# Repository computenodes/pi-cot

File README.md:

# Pi-iC880a

Adapter board to interface between the Raspberry Pi and the [iC880a LoRaWAN](https://wireless-solutions.de/products/radiomodules/ic880a.html) concentrator.  It also supports an EEPROM for HAT identification, DS3231 RTC chip for maintaining time between powercycles, and a [DHT-22](http://www.hobbytronics.co.uk/rht03-humidity-temp-sensor?keyword=dht22) for temperature/humidity sensing.

This board supports using 3 different GPS modules for the timing/positioning
 1. [Adafruit Ultimate GPS module](https://www.adafruit.com/product/746) soldered onto the board.  
 1. The MT3339 GPS modules (as used on the adafruit break out board) soldered directly to the PCB.  
 1. Ublox LEA-6T soldered onto the iC880a Concentrator.
 
 ## GPS Options
 In order to support the different GPS options there are solder jumpers on the PCB to link the required lines.  There are 3 jumpers: TX, RX, PPS.  The jumpers for TX & RX need to be used whichever GPS module is in use.  The PPS link is needed if using either the Ultimate GPS, or the MT3339.
 
 ## Backup battery options
 There are also pads for 0 ohm resistors to enable a choice of which peripherals have the backup battery connected.  These can either be popuplated with 0ohm resistors, or just bridged using solder.
 
 ## Enabling the UBlox module
 All GPIOs from the iC880a board are connected to the Pi.  In order to enable the UBlox module on the iC880a a couple of these need to be configured as shown below.
 
 | Pi I/O | Function | Pin State |
 | ------ | -------- | --------- |
 |  23    |  GPS  EN | HIGH      |
 |  27    | !GPS RST | HIGH      |

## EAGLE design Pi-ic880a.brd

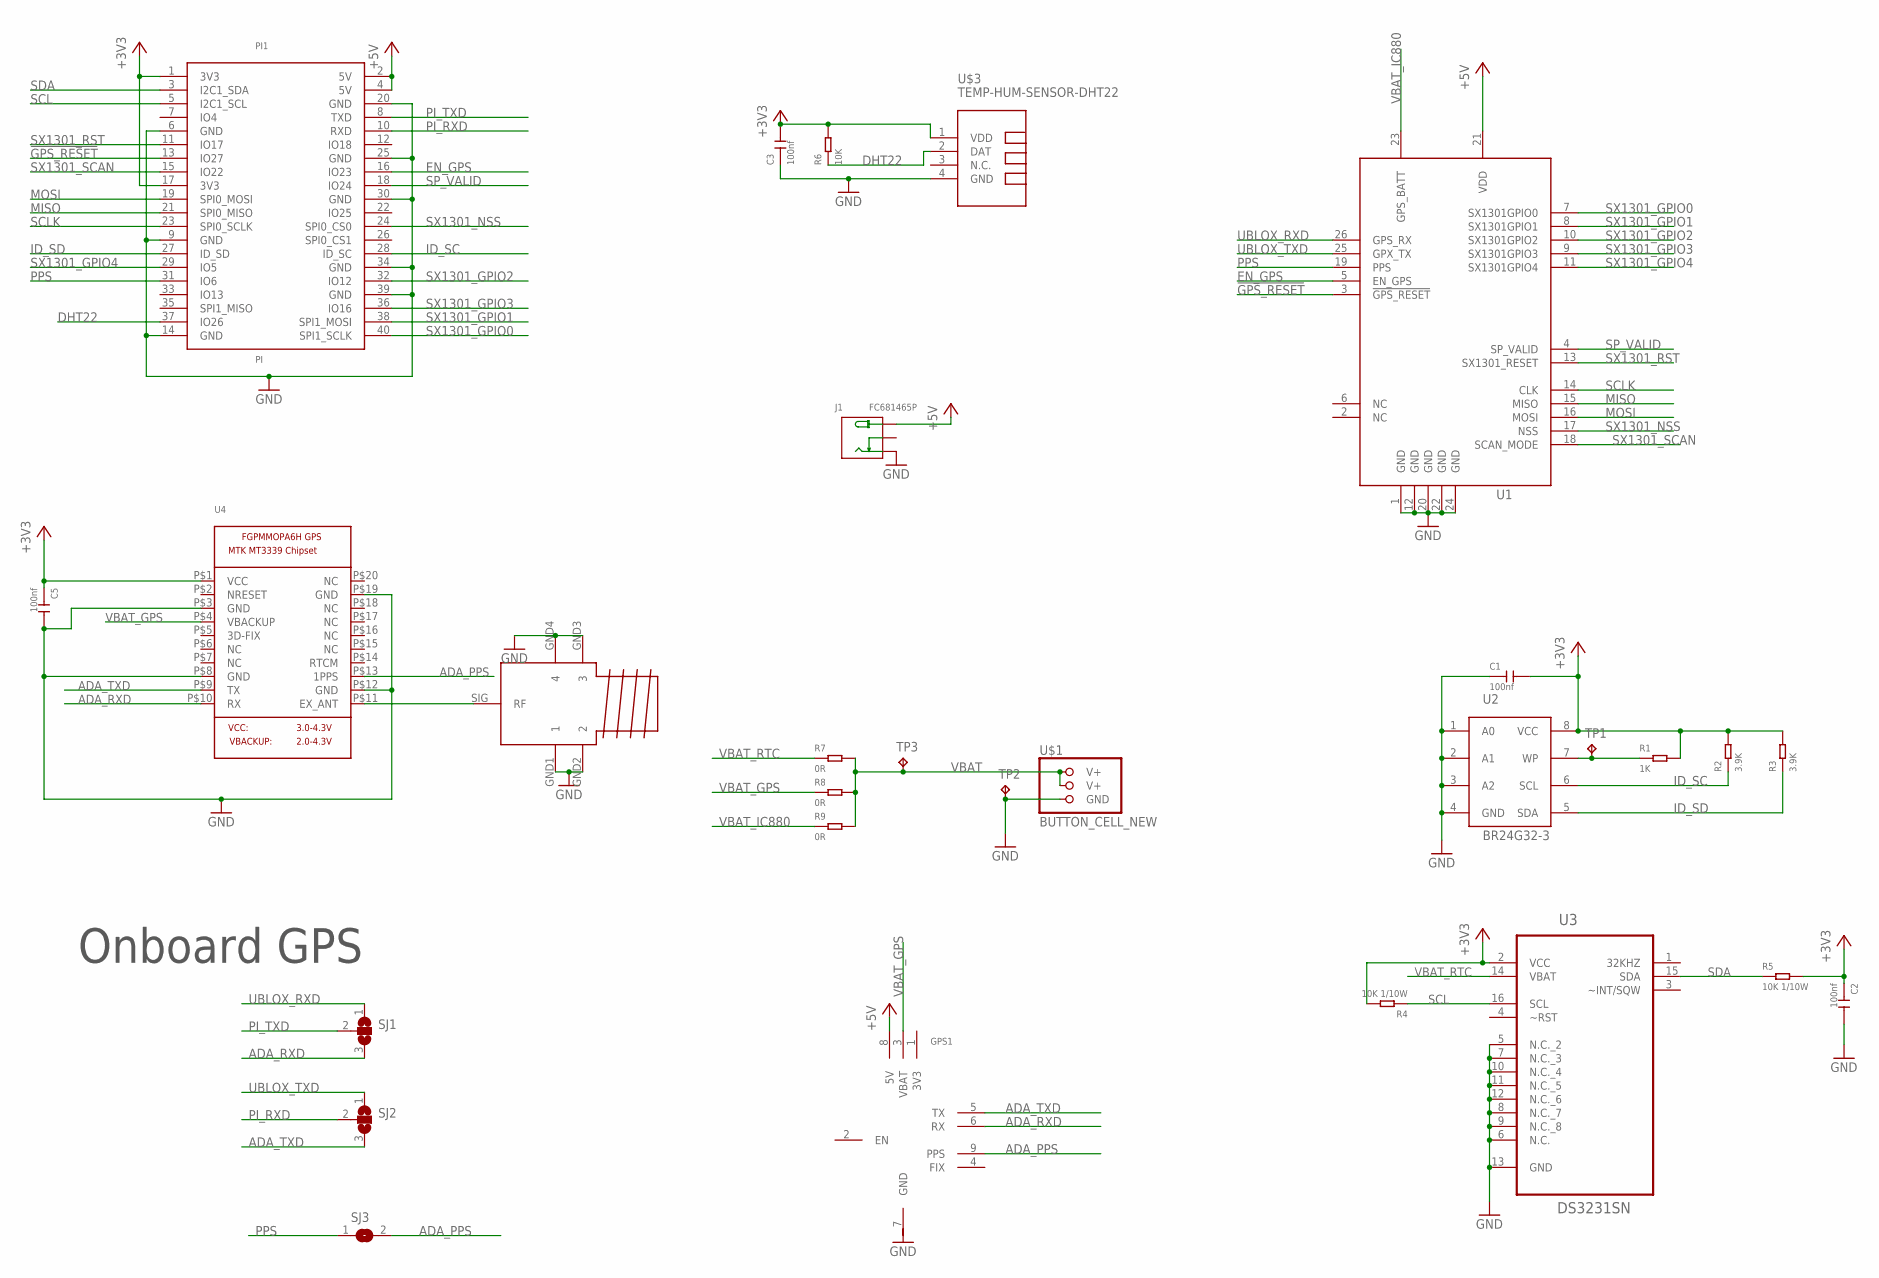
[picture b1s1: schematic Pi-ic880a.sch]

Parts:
C1, C2, C3, C5: 100nf; C0603
GPS1: ULTIMATE-GPS
J1: FC681465P
PI1: PI
R1: 1K; R0603
R2, R3: 3.9K; R0603
R4, R5: 10K 1/10W; R0603
R6: 10K; R0603
R7, R8, R9: 0R; R0603
SJ1, SJ2: SJ2W; SJ_2
SJ3: SJ
TP1, TP2, TP3: TPB2,54; B2,54
U1: IC880A
U2: BR24G32-3; SOP8
U3: DS3231SN; SOIC127P1032X265-16N
U4: GPS_FGPMMOPA6H; FGPMMOPA6H
U$1: BUTTON_CELL_NEW; CR2016
U$2: SMATH; SMA
U$3: TEMP-HUM-SENSOR-DHT22

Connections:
3V3: GPS1.1 (3V3)
!GPS_RESET: PI1.13 (IO27), U1.3 (!GPS_RESET)
+3V3: C1.2, C2.1, C3.2, C5.1, PI1.1 (3V3), PI1.17 (3V3), R1.2, R2.2, R3.2, R4.2, R5.2, R6.2, U2.8 (VCC), U3.2 (VCC), U4.P$1 (VCC), U$3.1 (VDD)
+5V: GPS1.8 (5V), J1.1 (+), PI1.2 (5V), PI1.4 (5V), U1.21 (VDD)
ADA_PPS: GPS1.9 (PPS), SJ3.2, U4.P$13 (1PPS)
ADA_RXD: GPS1.6 (RX), SJ1.3, U4.P$10 (RX)
ADA_TXD: GPS1.5 (TX), SJ2.3, U4.P$9 (TX)
DHT22: PI1.37 (IO26), R6.1, U$3.2 (DAT)
EN_GPS: PI1.16 (IO23), U1.5 (EN_GPS)
GND: C1.1, C2.2, C3.1, C5.2, GPS1.7 (GND), J1.3 (-), PI1.6 (GND), PI1.9 (GND), PI1.14 (GND), PI1.20 (GND), PI1.25 (GND), PI1.30 (GND), PI1.34 (GND), PI1.39 (GND), TP2.TP, U1.1 (GND), U1.12 (GND), U1.20 (GND), U1.22 (GND), U1.24 (GND), U2.1 (A0), U2.2 (A1), U2.3 (A2), U2.4 (GND), U3.5 (N.C._2), U3.6 (N.C.), U3.7 (N.C._3), U3.8 (N.C._7), U3.9 (N.C._8), U3.10 (N.C._4), U3.11 (N.C._5), U3.12 (N.C._6), U3.13 (GND), U4.P$3 (GND), U4.P$8 (GND), U4.P$12 (GND), U4.P$19 (GND), U$1.GND, U$2.GND1 (1), U$2.GND2 (2), U$2.GND3 (3), U$2.GND4 (4), U$3.4 (GND)
GPS_ANT: U4.P$11 (EX_ANT), U$2.SIG (RF)
ID_SC: PI1.28 (ID_SC), R2.1, U2.6 (SCL)
ID_SD: PI1.27 (ID_SD), R3.1, U2.5 (SDA)
MISO: PI1.21 (SPI0_MISO), U1.15 (MISO)
MOSI: PI1.19 (SPI0_MOSI), U1.16 (MOSI)
PI_RXD: PI1.10 (RXD), SJ2.2
PI_TXD: PI1.8 (TXD), SJ1.2
PPS: PI1.31 (IO6), SJ3.1, U1.19 (PPS)
SCL: PI1.5 (I2C1_SCL), R4.1, U3.16 (SCL)
SCLK: PI1.23 (SPI0_SCLK), U1.14 (CLK)
SDA: PI1.3 (I2C1_SDA), R5.1, U3.15 (SDA)
SP_VALID: PI1.18 (IO24), U1.4 (SP_VALID)
SX1301_GPIO0: PI1.40 (SPI1_SCLK), U1.7 (SX1301GPIO0)
SX1301_GPIO1: PI1.38 (SPI1_MOSI), U1.8 (SX1301GPIO1)
SX1301_GPIO2: PI1.32 (IO12), U1.10 (SX1301GPIO2)
SX1301_GPIO3: PI1.36 (IO16), U1.9 (SX1301GPIO3)
SX1301_GPIO4: PI1.29 (IO5), U1.11 (SX1301GPIO4)
SX1301_NSS: PI1.24 (SPI0_CS0), U1.17 (NSS)
SX1301_RST: PI1.11 (IO17), U1.13 (SX1301_RESET)
SX1301_SCAN: PI1.15 (IO22), U1.18 (SCAN_MODE)
UBLOX_RXD: SJ1.1, U1.26 (GPS_RX)
UBLOX_TXD: SJ2.1, U1.25 (GPX_TX)
VBAT: R7.2, R8.2, R9.2, TP3.TP, U$1.V+@1 (V+), U$1.V+@2 (V+)
VBAT_GPS: GPS1.3 (VBAT), R8.1, U4.P$4 (VBACKUP)
VBAT_IC880: R9.1, U1.23 (GPS_BATT)
VBAT_RTC: R7.1, U3.14 (VBAT)
WP: R1.1, TP1.TP, U2.7 (WP)

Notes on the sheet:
Onboard GPS

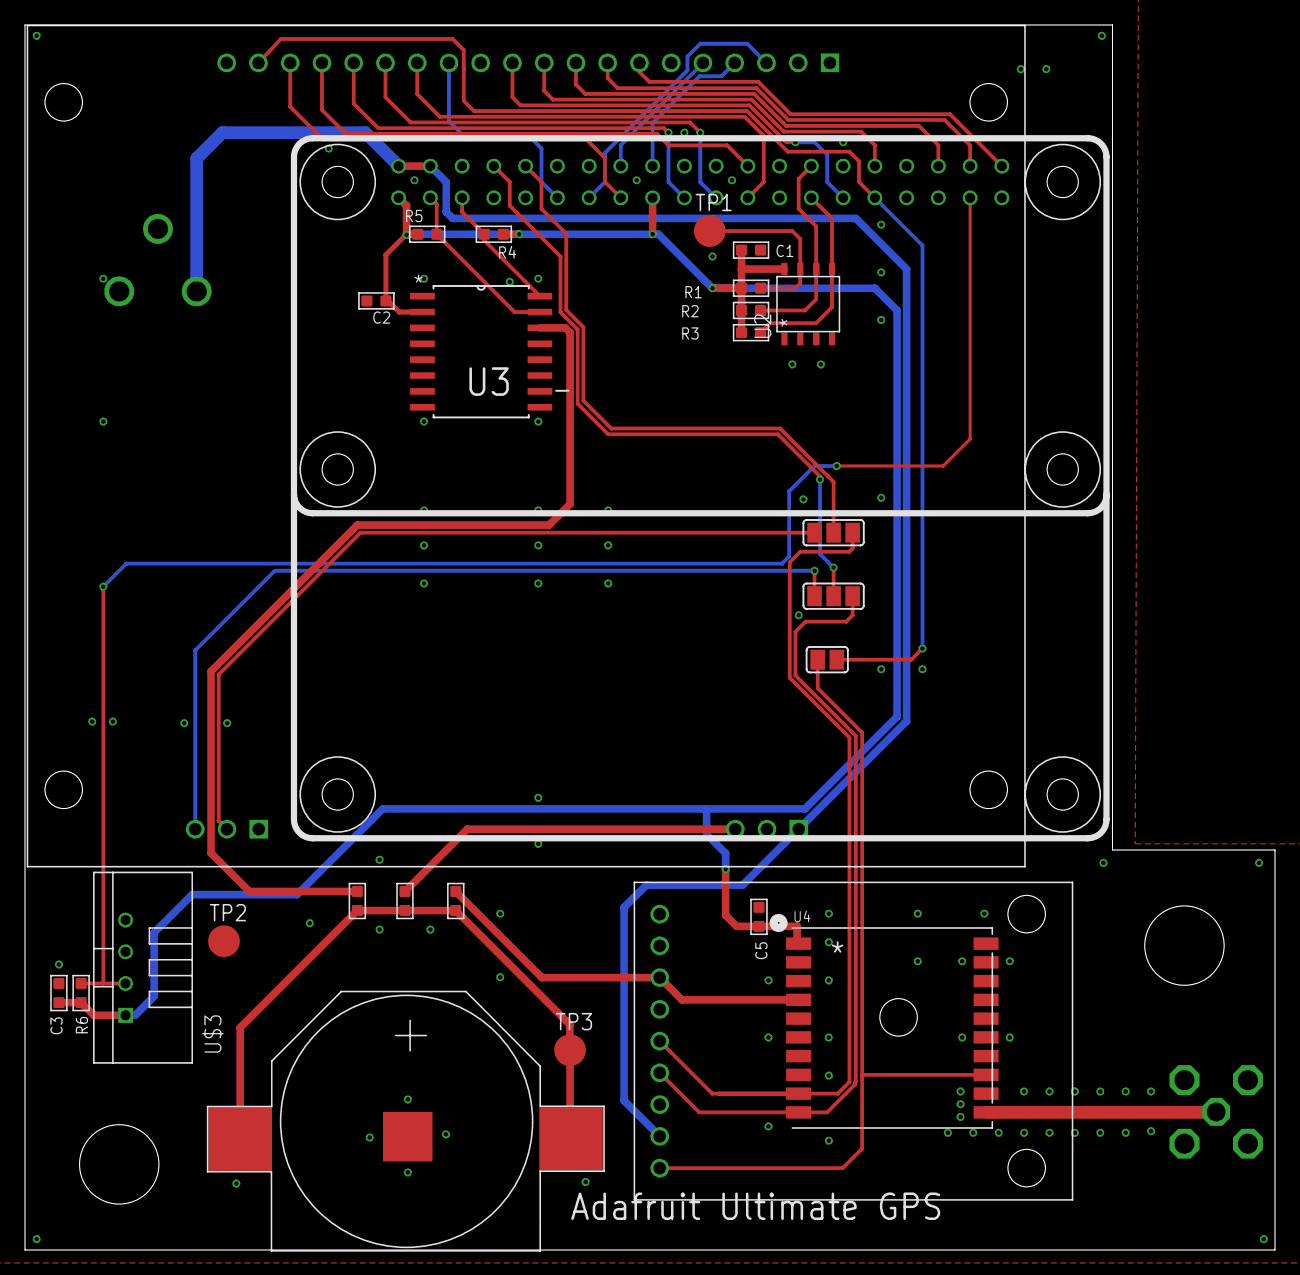
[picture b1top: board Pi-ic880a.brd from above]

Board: 2 copper layers, 100.0 x 98.0 mm, 29 parts (1 on the bottom side), 36 nets.

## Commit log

2017-07-25 updated to be more comprehensive
2017-07-25 First thoughts about multi-gps adapter board
2017-08-01 Standalone version of the adafruit GPS module added
2017-08-15 Now uses ds3231 as RTC
2017-10-16 DHT22 added now fully laid out and ready for final check through
2017-10-23 Added jumpers for BAT more work on labelling added test pads for VBAT
2017-10-23 After adding all other GPIO
2017-10-23 as submitted
2017-11-10 layout names / values a bit better
2017-11-10 placement file
2017-11-10 first version of test schedule
2017-11-10 Mounting holes for adafruit module now corrected
2017-11-16 first version of hat eeprom spec
2017-11-17 Layout tweaks
2017-11-20 V2 about ready to go
2017-11-20 updates to test schedule
2017-11-22 DC jack added Now called Pi-CoT smd GPS moved closer to ant holes for Pi connector now bigger
2017-11-22 elecrow dru added
2017-11-22 V2 as submitted
2018-03-05 zip file as submitted
2018-03-05 Create LICENSE
    CC-BY-SA
2019-01-21 Add DOI badge
2019-02-19 Rename to be Pi-CoT
